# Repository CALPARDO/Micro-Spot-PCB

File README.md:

# Top

# Bottom

## 3D File
[Click](https://a360.co/3aaRJEH)

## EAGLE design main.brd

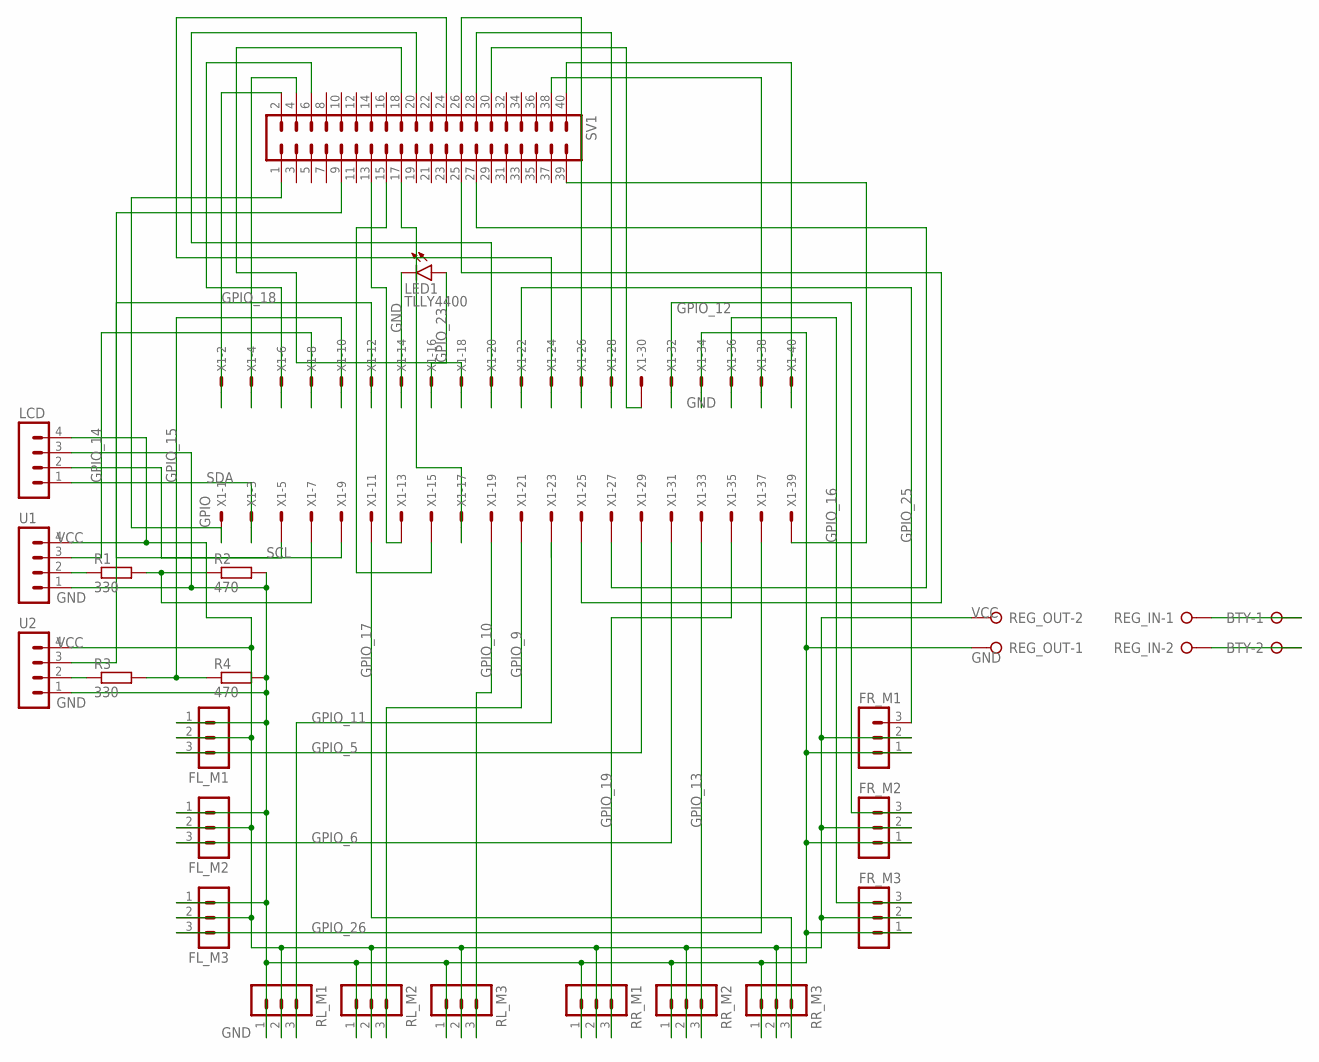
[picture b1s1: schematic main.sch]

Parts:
BTY: W237-02P; W237-132
FL_M1, FL_M2, FL_M3: MA03-1
FR_M1, FR_M2, FR_M3: MA03-1
LCD: MA04-1
LED1: TLLY4400; LED3MM
R1, R3: 330; 0204/7
R2, R4: 470; 0204/7
REG_IN: W237-02P; W237-132
REG_OUT: W237-02P; W237-132
RL_M1, RL_M2, RL_M3: MA03-1
RR_M1, RR_M2, RR_M3: MA03-1
SV1: MA20-2
U1, U2: MA04-1
X1: GPIO; 057-040-1

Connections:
E1: R1.1, U1.2
GND: FL_M1.1, FL_M2.1, FL_M3.1, FR_M1.1, FR_M2.1, FR_M3.1, LCD.3, LED1.K (C), R2.2, R4.2, REG_OUT.1, RL_M1.1, RL_M2.1, RL_M3.1, RR_M1.1, RR_M2.1, RR_M3.1, U1.1, U2.1, X1.14, X1.34
GPIO_5: FL_M1.3, X1.29
GPIO_6: FL_M2.3, X1.31
GPIO_9: RL_M2.3, X1.21
GPIO_10: RL_M3.3, X1.19
GPIO_11: RL_M1.3, X1.23
GPIO_12: FR_M2.3, X1.32
GPIO_13: RR_M2.3, X1.33
GPIO_14: U1.3, X1.8
GPIO_15: R3.2, R4.1, X1.10
GPIO_16: FR_M3.3, X1.36
GPIO_17: RR_M3.3, X1.11
GPIO_18: U2.3, X1.12
GPIO_19: RR_M1.3, X1.35
GPIO_23: LED1.A, X1.16
GPIO_25: FR_M1.3, X1.22
GPIO_26: FL_M3.3, X1.37
unnamed: R3.1, U2.2
unnamed: R1.2, R2.1, X1.7
unnamed: SV1.2, X1.2
unnamed: SV1.4, X1.4
unnamed: SV1.6, X1.6
unnamed: SV1.18, X1.18
unnamed: SV1.20, X1.20
unnamed: SV1.24, X1.24
unnamed: SV1.26, X1.26
unnamed: SV1.28, X1.28
unnamed: SV1.30, X1.30
unnamed: SV1.40, X1.40
unnamed: SV1.38, X1.38
unnamed: SV1.39, X1.39
unnamed: BTY.1, REG_IN.1
unnamed: BTY.2, REG_IN.2
unnamed: SV1.27, X1.27
unnamed: SV1.25, X1.25
unnamed: SV1.1, X1.1
unnamed: SV1.9, X1.9
unnamed: SV1.13, X1.13
unnamed: SV1.15, X1.15
unnamed: SV1.17, X1.17
SCL: LCD.2, X1.5
SDA: LCD.1, X1.3
VCC: FL_M1.2, FL_M2.2, FL_M3.2, FR_M1.2, FR_M2.2, FR_M3.2, LCD.4, REG_OUT.2, RL_M1.2, RL_M2.2, RL_M3.2, RR_M1.2, RR_M2.2, RR_M3.2, U1.4, U2.4

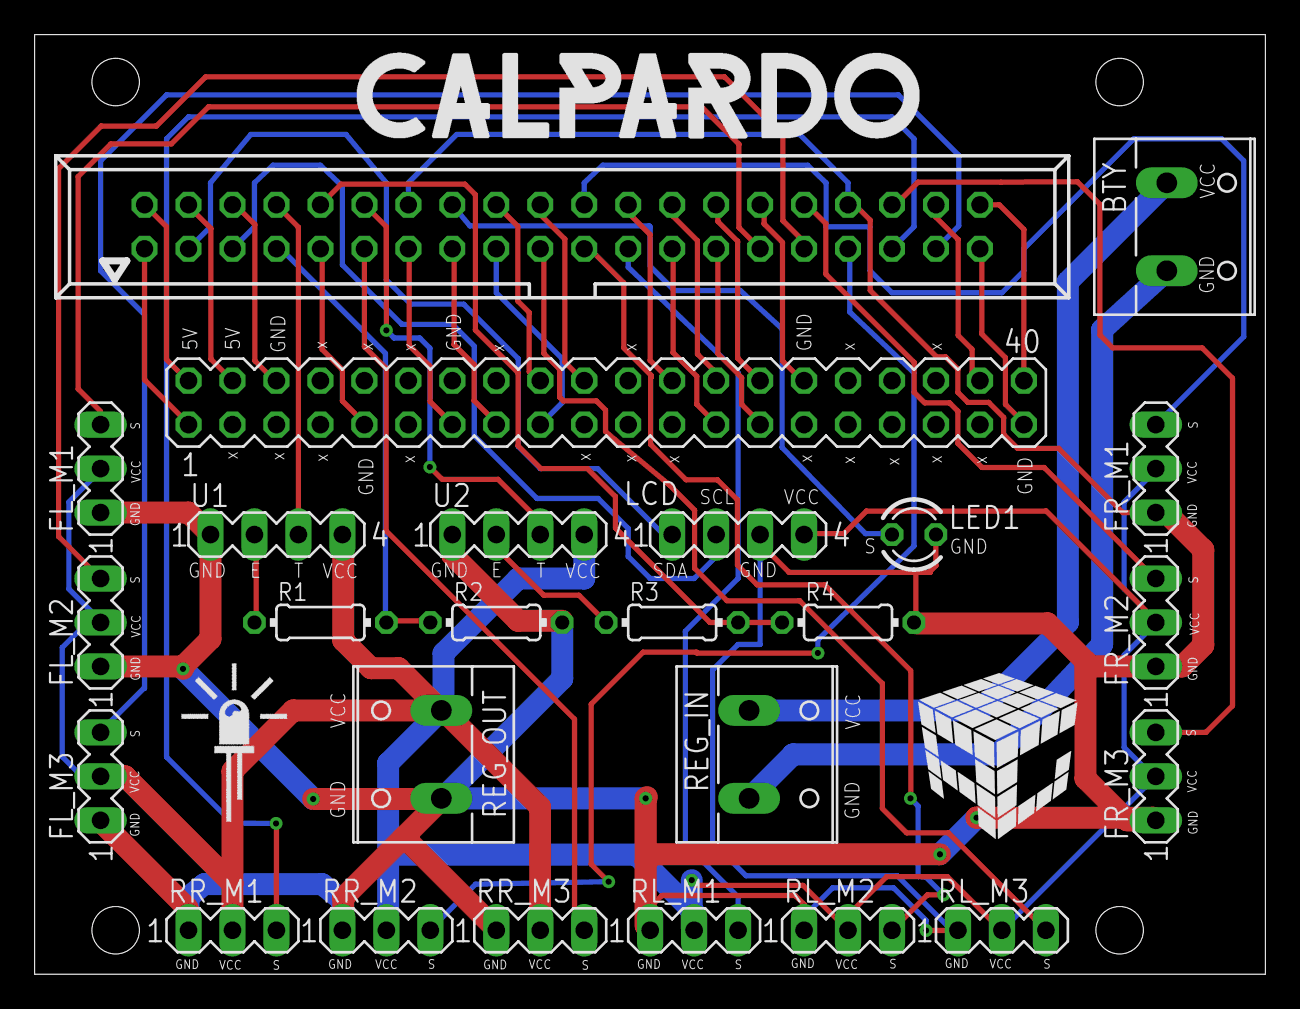
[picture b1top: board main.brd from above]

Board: 2 copper layers, 71.1 x 54.3 mm, 25 parts (0 on the bottom side), 44 nets.

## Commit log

2021-02-13 Rename routed.brd to main.brd
2021-02-13 Rename routed.sch to main.sch
2021-02-15 Renders added
